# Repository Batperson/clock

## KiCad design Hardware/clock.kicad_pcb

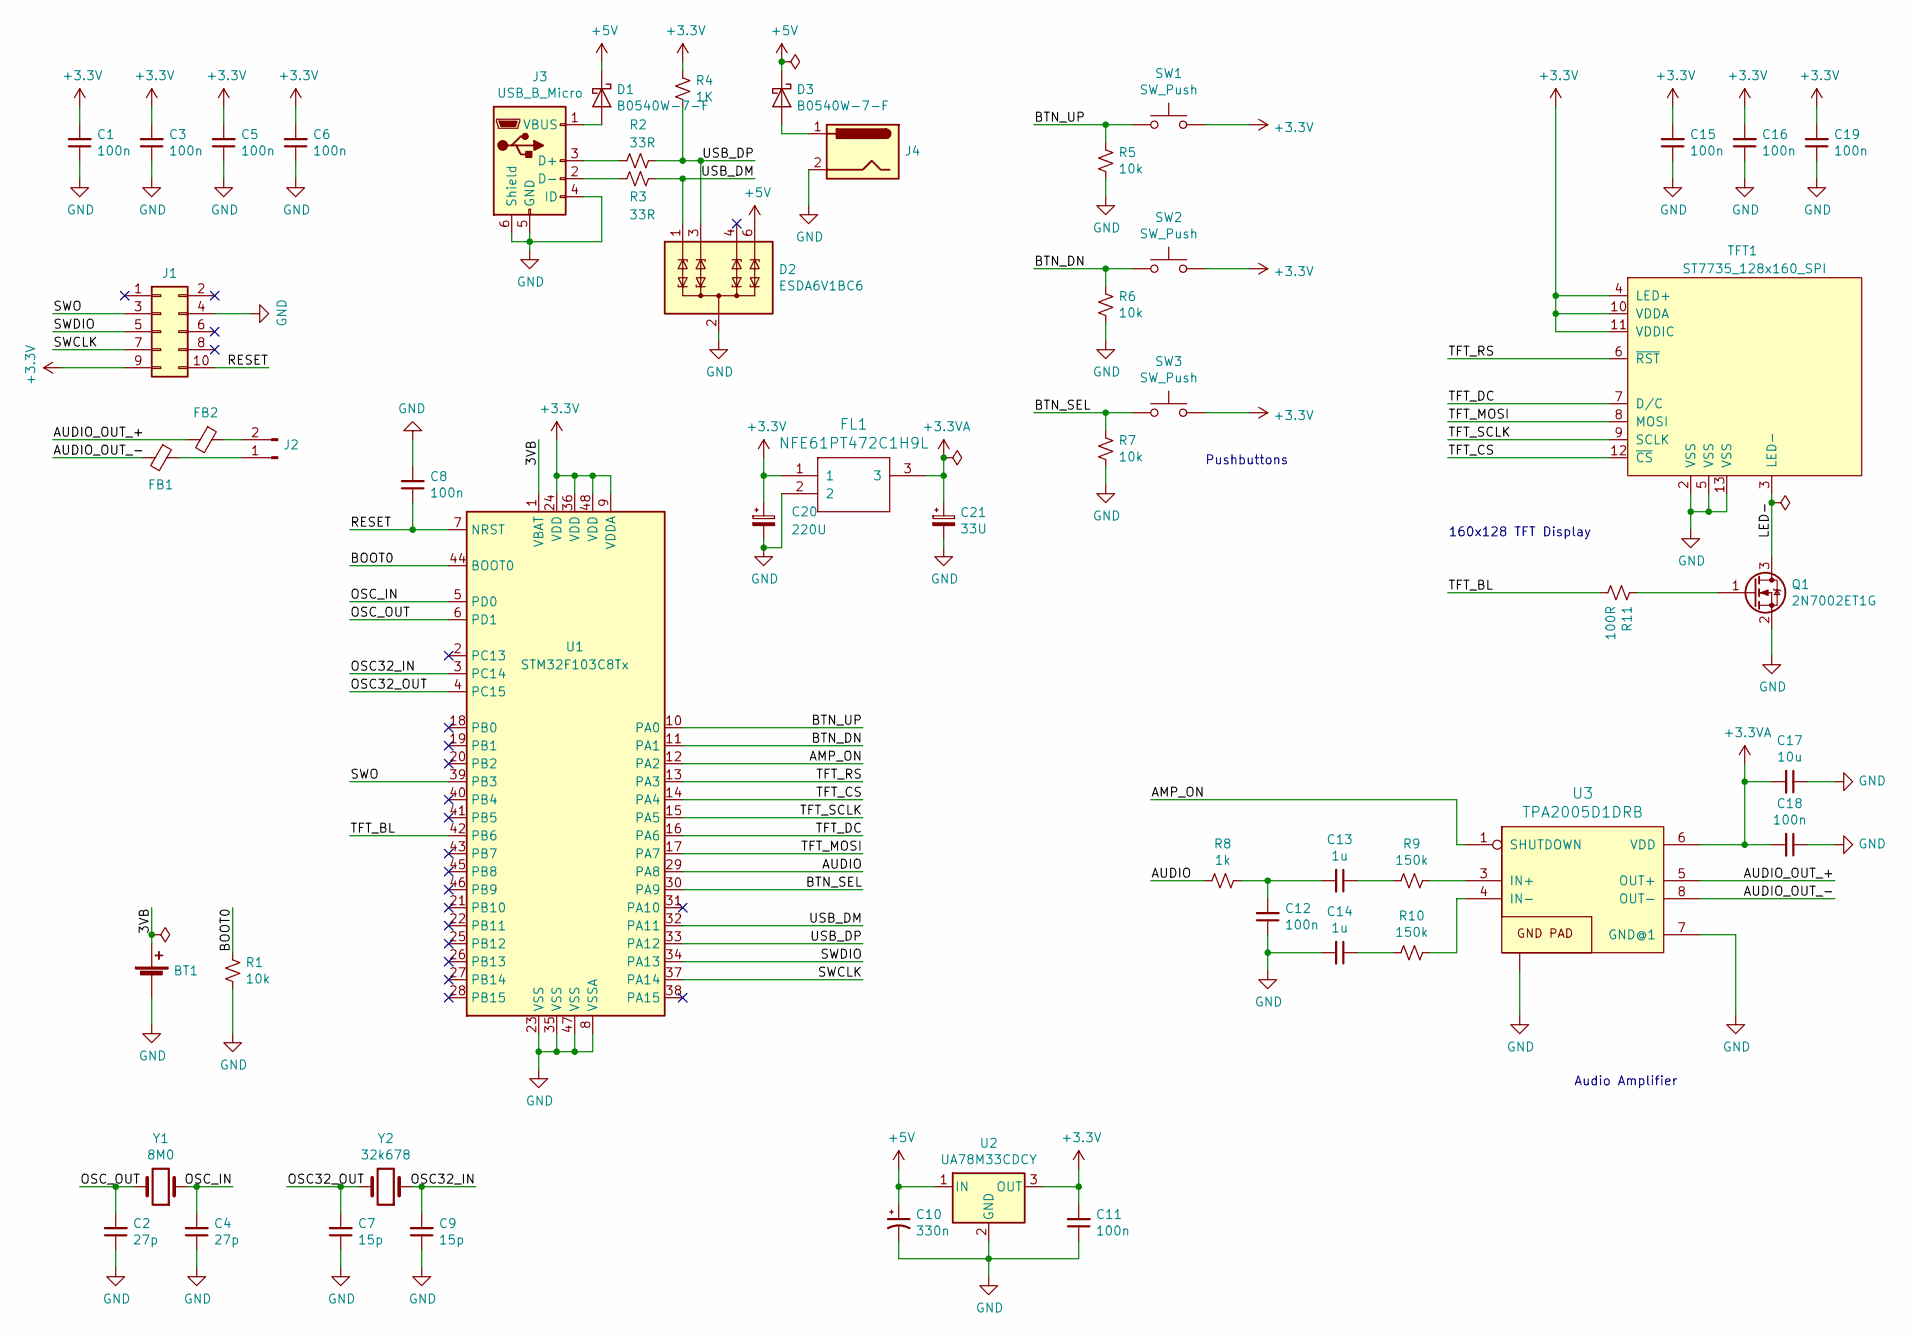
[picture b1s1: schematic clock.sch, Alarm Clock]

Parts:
BT1: Battery_Cell; BatteryHolder_Keystone_3000_1x12mm
C1, C3, C5, C6, C8, C11, C12, C15, C16, C18, C19: 100n; C_0402_1005Metric
C2, C4: 27p; C_0402_1005Metric
C7, C9: 15p; C_0402_1005Metric
C10: 330n; C_0402_1005Metric
C13, C14: 1u; C_0402_1005Metric
C17: 10u; C_0402_1005Metric
C20: 220U; CP_EIA-7343-20_Kemet-V_Pad2.25x2.55mm_HandSolder
C21: 33U; CP_EIA-3528-21_Kemet-B_Pad1.50x2.35mm_HandSolder
D1, D3: B0540W-7-F; D_SOD-123
D2: ESDA6V1BC6; SOT-23-6
FB1, FB2: BLM18PG471SN1D; R_0603_1608Metric_Pad1.05x0.95mm_HandSolder
FL1: NFE61PT472C1H9L; 6816
J1: Conn_02x05_Counter_Clockwise; PinHeader_2x05_P2.54mm_Vertical
J2: Conn_01x02_Male; PinHeader_1x02_P2.54mm_Horizontal
J3: USB_B_Micro; USB_Micro-B_Molex_47346-0001
J4: Barrel_Jack; DC-005-SMT
Q1: 2N7002ET1G; SOT-23_Handsoldering
R1, R5, R6, R7: 10k; R_0603_1608Metric
R2, R3: 33R; R_0603_1608Metric
R4: 1K; R_0603_1608Metric
R8: 1k; R_0603_1608Metric
R9, R10: 150k; R_0603_1608Metric
R11: 100R; R_0603_1608Metric
SW1, SW2, SW3: SW_Push; SW_Push_1P1T_NO_6x6mm_H9.5mm
TFT1: ST7735_128x160_SPI; TFT_160x120_14pin
U1: STM32F103C8Tx; LQFP-48_7x7mm_P0.5mm
U2: UA78M33CDCY; SOT-223-3_TabPin2
U3: TPA2005D1DRB; MSOP-8-1EP_3x3mm_P0.65mm_EP1.73x1.85mm
Y1: 8M0; Crystal_HC49-U_Vertical
Y2: 32k678; Crystal_SMD_3215-2Pin_3.2x1.5mm

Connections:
+3.3VA: C17.2, C18.2, C21.1, FL1.3, U3.6 (VDD)
+3V3: C1.2, C3.2, C5.2, C6.2, C11.2, C15.2, C16.2, C19.2, C20.1, FL1.1, J1.9, R4.2, SW1.2, SW2.2, SW3.2, TFT1.4 (LED+), TFT1.10 (VDDA), TFT1.11 (VDDIC), U1.9 (VDDA), U1.24 (VDD), U1.36 (VDD), U1.48 (VDD), U2.3 (OUT)
+5V: C10.1, D1.1 (K), D2.6 (TVS4), D3.1 (K), U2.1 (IN)
/3VB: BT1.1 (+), U1.1 (VBAT)
/AMP_ON: U1.12 (PA2), U3.1 (SHUTDOWN)
/AUDIO: R8.2, U1.29 (PA8)
/AUDIO_OUT_+: FB2.2, U3.5 (OUT+)
/AUDIO_OUT_-: FB1.2, U3.8 (OUT-)
/BOOT0: R1.2, U1.44 (BOOT0)
/BTN_DN: R6.2, SW2.1, U1.11 (PA1)
/BTN_SEL: R7.2, SW3.1, U1.30 (PA9)
/BTN_UP: R5.2, SW1.1, U1.10 (PA0)
/LED-: Q1.3 (D), TFT1.3 (LED-)
/OSC32_IN: C9.2, U1.3 (PC14), Y2.1
/OSC32_OUT: C7.2, U1.4 (PC15), Y2.2
/OSC_IN: C4.2, U1.5 (PD0), Y1.1
/OSC_OUT: C2.2, U1.6 (PD1), Y1.2
/RESET: C8.1, J1.10, U1.7 (NRST)
/SWCLK: J1.7, U1.37 (PA14)
/SWDIO: J1.5, U1.34 (PA13)
/SWO: J1.3, U1.39 (PB3)
/TFT_BL: R11.1, U1.42 (PB6)
/TFT_CS: TFT1.12 (~CS), U1.14 (PA4)
/TFT_DC: TFT1.7 (D/C), U1.16 (PA6)
/TFT_MOSI: TFT1.8 (MOSI), U1.17 (PA7)
/TFT_RS: TFT1.6 (~RST), U1.13 (PA3)
/TFT_SCLK: TFT1.9 (SCLK), U1.15 (PA5)
/USB_DM: D2.1 (TVS1), R3.2, U1.32 (PA11)
/USB_DP: D2.3 (TVS2), R2.2, R4.1, U1.33 (PA12)
GND: BT1.2 (-), C1.1, C2.1, C3.1, C4.1, C5.1, C6.1, C7.1, C8.2, C9.1, C10.2, C11.1, C12.1, C14.2, C15.1, C16.1, C17.1, C18.1, C19.1, C20.2, C21.2, D2.2 (COM), D2.5 (COM), FL1.2, J1.4, J3.4 (ID), J3.5 (GND), J3.6 (Shield), J4.2, Q1.2 (S), R1.1, R5.1, R6.1, R7.1, TFT1.2 (VSS), TFT1.5 (VSS), TFT1.13 (VSS), U1.8 (VSSA), U1.23 (VSS), U1.35 (VSS), U1.47 (VSS), U2.2 (GND), U3.7 (GND@1), U3.9 (GND@2)
unnamed: C12.2, C13.2, R8.1
unnamed: C13.1, R9.2
unnamed: C14.1, R10.2
unnamed: D1.2 (A), J3.1 (VBUS)
unnamed: D3.2 (A), J4.1
unnamed: FB1.1, J2.1
unnamed: FB2.1, J2.2
unnamed: J3.2 (D-), R3.1
unnamed: J3.3 (D+), R2.1
unnamed: Q1.1 (G), R11.2
unnamed: R9.1, U3.3 (IN+)
unnamed: R10.1, U3.4 (IN-)

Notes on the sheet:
Audio Amplifier
160x128 TFT Display
Pushbuttons

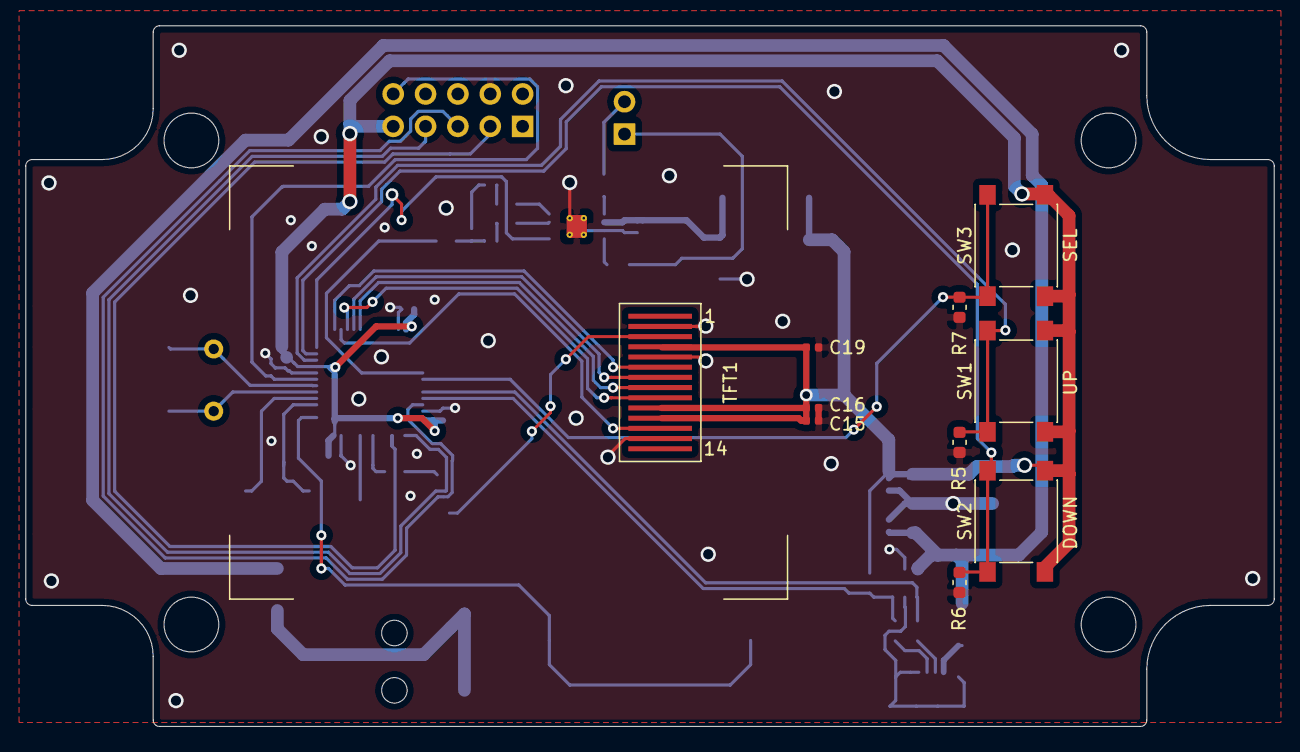
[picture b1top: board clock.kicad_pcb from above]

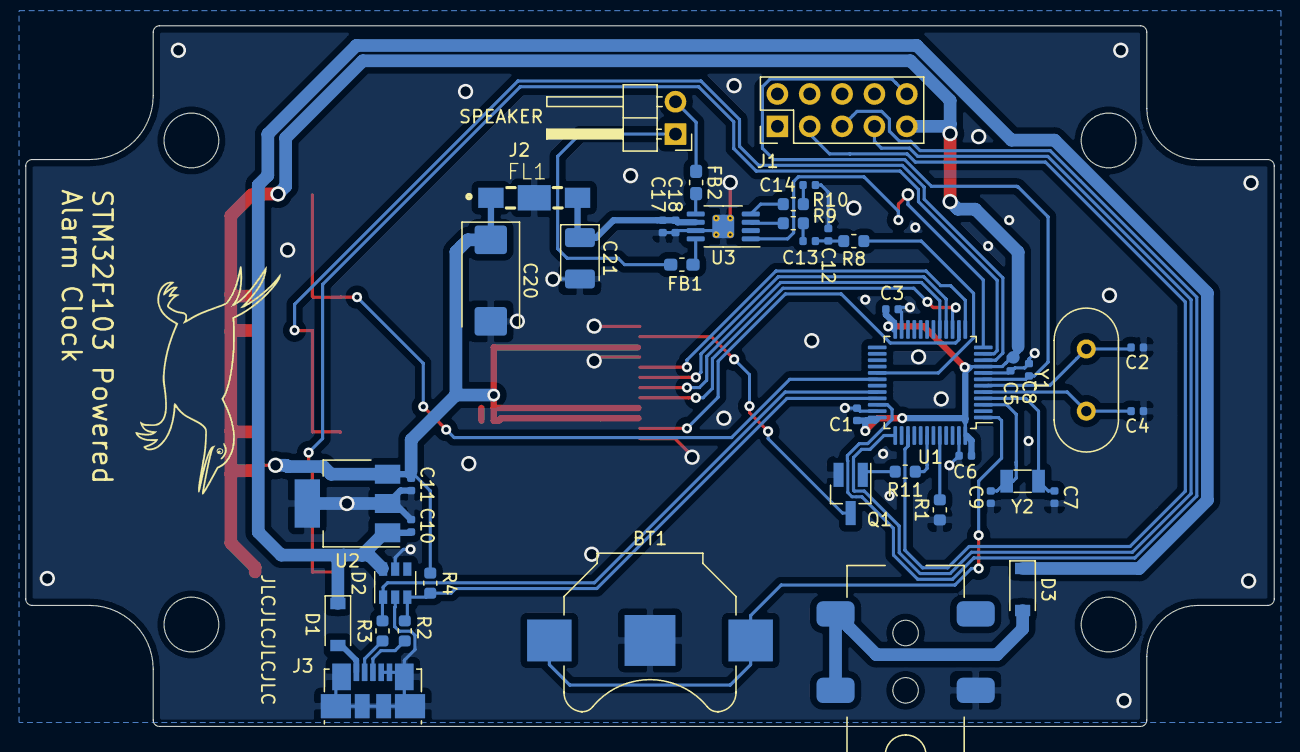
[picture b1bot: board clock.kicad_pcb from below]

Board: 2 copper layers, 98.0 x 55.0 mm, 53 parts (43 on the bottom side), 42 nets.

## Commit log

2019-10-13 Implemented sound, implementing songs
2019-10-14 Implemented song playback
2019-10-17 Voices support attack and decay envelope parameters
2019-10-19 Song playback implemented
2019-10-20 Tidy up
2019-10-26 More music
2019-10-28 Implemented button firmware
2019-11-02 Button firmware working
2019-11-02 Implemented timed beep
2019-11-08 Clock state framework, reorganization
2019-11-09 Menu system now working
2019-11-15 Changed menu system to support submenus, variable length
2019-11-16 Clock set functionality working
2019-11-17 The same track can be layered more than once, with a tempo offset
2019-11-17 Alarm ring preview implemented
2019-11-22 Implemented alarm
2019-11-22 Updated to alarm
2019-11-23 Alarm ring working
2019-11-26 Revised the button callback system
2019-11-26 Fix issue where multiple button down events occurred with only 1 button press.
2019-11-26 More button fixes
2019-11-29 Graphics now using a simple HAL. Support right and centre-aligned text. Moved font data into ROM.
2019-11-30 Revised button handlers again. Now support multiple events per handler. Can hold button down to quickly increment or decrement a value when setting time, date or alarm.
2019-11-30 Fix issue where multiple events occur after changing the button handler
2019-11-30 Change to RTC alarm setting
2019-11-30 Can now save alarm ring
2019-12-08 Revamped the callback timeout system. Misc changes.
2019-12-13 Small tweaks
2019-12-20 Alarm lock implemented
2019-12-22 Consolidated alarm and clock modes
2019-12-22 Now implemented save/restore of settings in backup domain
2019-12-23 Implemented special day message banner
2019-12-26 Replace roll-my-own swap function with CMSIS version
2019-12-26 Fixed re-entrancy issue with special day messages
2019-12-29 Support dynamic menu display sizes
2019-12-29 Support new 160 * 128 TFT display
2019-12-29 Tweak to special day text fade effect
2019-12-30 Adjust screen positions
2020-01-02 Update to menu ui. Full support
2020-01-06 Implemented am/pm display
2020-01-06 Implemented bitmap drawing
2020-01-07 Changed menu system to show selected items with a flag
2020-01-08 Implemented alarm icons, and misc tweaks
2020-01-10 Started new song Baby Shark
2020-01-11 Completed Baby Shark, third bar changed chord to C major from E minor as it sounds better.
2020-01-11 Fixed double-start of alarm rings when previewing with the menu.
2020-01-12 New song Gravity Falls
2020-01-13 New song Happy Birthday
2020-01-15 New song: NZ national anthem
2020-01-17 Tweaked the songs
2020-01-18 Added amplifier shutdown pin A2
2020-01-18 New clipped sine voice, other tweaks
2020-01-25 Small tweaks. Started new song Star Wars.
2020-01-25 Started on hardware schematic + board design.
2020-01-25 Added MCU, amplifier to schematic.
2020-01-25 Begun new song Into The Unknown
2020-01-26 Fixed a bad note definition. More of Into The Unknown.
2020-01-26 More of Into The Unknown
2020-01-27 Small tweaks. All rendering back in render.c. More of Into the Unknown.
2020-01-30 Implemented an advanced drawtext for gradient fills, etc
2020-01-30 More on Into The Unknown
2020-01-30 Implemented stripe brush
2020-02-01 Implemented an About image. Added icons to source.
2020-02-02 Fixed issue with DrawBitmap. About screen now rendering. Implemented gradient brush.
2020-02-04 Implemented gradient brush. Implemented about screen.
2020-02-06 Song tweaks, implementation of oscillator calibration and snooze minutes menu options
2020-02-07 Small fixes
2020-02-08 Revised the field set system. Tweak to Star Wars.
2020-02-08 Tweak to brush callback function, to return colours as a 32-bit struct which will hopefully optimize to 1 register
2020-02-08 Fix one song title which was too long
2020-02-16 Implemented backlight PWM brightness control
2020-02-21 Changes to schematic. Implemented display dimming and menu items to control dimming.
2020-02-22 Small fixes to brightness control
2020-02-22 Another fix to brightness settings
2020-02-28 Updated schematic
2020-03-13 Finished schematic. Begun routing. Added enclosure design files from vendor.
2020-03-15 Added filter for amplifier supply. Some routing.
2020-03-21 Routing complete
2020-03-24 DC jack was round the wrong way. Added proper step model for it. Added Freecad model.
2020-03-28 Added FreeCAD model of enclosure + PCB. Small changes to PCB layout. Added STEP model of TFT display.
2020-03-28 Added weka to silkscreen.
2020-07-15 Small changes to code after populating board. Hardware should be unchanged.
2020-07-21 Untested fix for crash which occurs when setting the date if the special day text is showing.
2020-08-02 Amp is disabled when no sound playing, to avoid annoying whine. Fixed crash when selecting Random Song menu item. Workaround for misaligned screen. New build for Rosie, with specific special days.
2020-08-02 Fix for alarm ring not playing
2020-08-04 Added quick way to skip through special day texts
2020-08-07 Fix for screen garbage when exiting About screen. Running out of memory so removed the lowercase letters from sysFont. Change to alarm snooze functionality. Misc. fixes.
2020-08-08 Rendering fixes
2020-08-09 Date and render fixes
2020-08-09 Create LICENSE
2020-08-09 Changed launch config
